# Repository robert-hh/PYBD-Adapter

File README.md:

## PYBD-Adapter: Adapter between 1/20" and 1/10" pitch of the side connectors
    
Two Variants: Small and Wide.

The Small one has a 0.3" distance between the 0.1" Sockets, leaving more
2-3 rows available on a breadboard. It has to be assembled on the top
side of the PYBD.

The Wide one has a 0.8" distance, allowing (partially) stacking headers,
but leaving only 1 row free on a breadboard and may be assembled on
either side of the PYBD.

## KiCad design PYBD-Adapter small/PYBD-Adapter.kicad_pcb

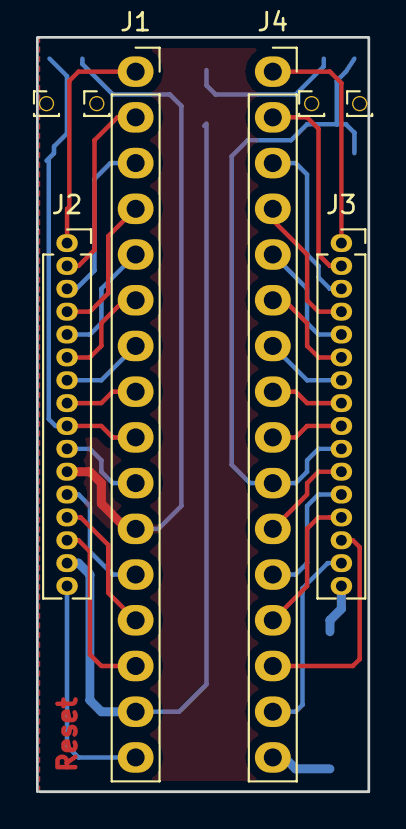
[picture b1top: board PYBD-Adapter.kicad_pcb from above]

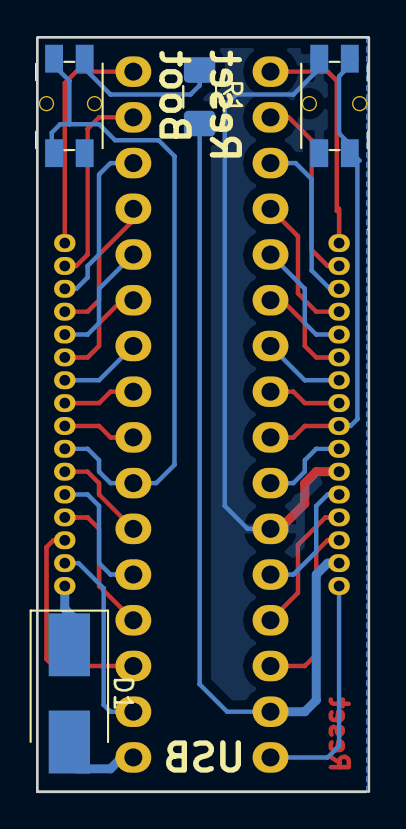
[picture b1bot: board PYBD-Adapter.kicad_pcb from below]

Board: 2 copper layers, 18.4 x 41.9 mm, 8 parts (4 on the bottom side), 34 nets.

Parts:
D1: 1N5817; D_SMB_Handsoldering
J1, J4: Socket Strip 0.1"; PinSocket_1x16_P2.54mm_Vertical
J2, J3: Socket Strip 0.05"; PinSocket_1x16_P1.27mm_Vertical
R1: 51k; R_1206_3216Metric_Pad1.42x1.75mm_HandSolder
SW1: Reset; Panasonic_EVQPUJ_EVQPUA
SW2: Boot; Panasonic_EVQPUJ_EVQPUA

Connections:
GND: J1.11, J2.11, SW1.2
unnamed: D1.1, J3.16
unnamed: D1.2, J4.16
unnamed: J1.1, J2.1
unnamed: J1.2, J2.2
unnamed: J1.3, J2.3
unnamed: J1.4, J2.4
unnamed: J1.5, J2.5
unnamed: J1.6, J2.6
unnamed: J1.7, J2.7
unnamed: J1.8, J2.8
unnamed: J1.9, J2.9, SW1.1
unnamed: J1.10, J2.10
unnamed: J1.12, J2.12
unnamed: J1.13, J2.13
unnamed: J1.14, J2.14
unnamed: J1.15, J2.15, R1.2
unnamed: J1.16, J2.16
unnamed: J3.1, J4.1
unnamed: J3.2, J4.2
unnamed: J3.3, J4.3
unnamed: J3.4, J4.4
unnamed: J3.5, J4.5
unnamed: J3.6, J4.6
unnamed: J3.7, J4.7
unnamed: J3.8, J4.8
unnamed: J3.9, J4.9
unnamed: J3.10, J4.10, SW2.1
unnamed: J3.11, J4.11
unnamed: J3.12, J4.12
unnamed: J3.13, J4.13
unnamed: J3.14, J4.14
unnamed: J3.15, J4.15
unnamed: R1.1, SW2.2

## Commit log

2019-06-16 PYBD-Adapter: Adapter between 1/20" and 1/10" pitch of the side connectors
    Two Variants: Small and Wide.
    The Small one has a 0.3" distance between the 0.1" Sockets, leaving more
    2-3 rows available on a breadboard. It has to be assembled on the top
    side of the PYBD.
    The Wide one has a 0.8" distance, allowing (partially) stacking headers,
    but leaving only 1 row free on a breadboard and may be assembled on
2019-06-16 README.md: Added
2019-10-20 Small Adapter: Add switches for reset and boot
    Change diode pad to hold SMD parts.
2019-10-22 Small Adapter: Add mounting holes for the switch
